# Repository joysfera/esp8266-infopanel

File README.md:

# esp8266-infopanel
WiFi LED information panel built on ESP8266

Using either WS2812 kind of LED strip or MAX7219 based LED matrix modules.

Video presentation in Czech language here: https://youtu.be/nCY0f-b_-vU

Updated exactly a year later for OpenAlt 2019 - added complete application
"clock" using NodeMCU modules u8g2d, sntp, rtctime and enduser_setup.

MicroUSB connector that fits to the PCB is BI0001715, found e.g. here https://www.aliexpress.com/i/32763236347.html

petr@pstehlik.cz

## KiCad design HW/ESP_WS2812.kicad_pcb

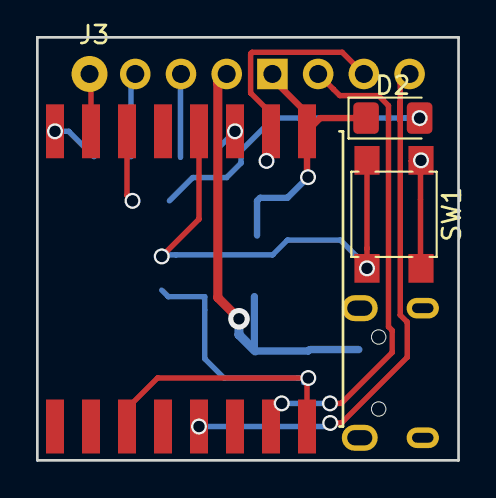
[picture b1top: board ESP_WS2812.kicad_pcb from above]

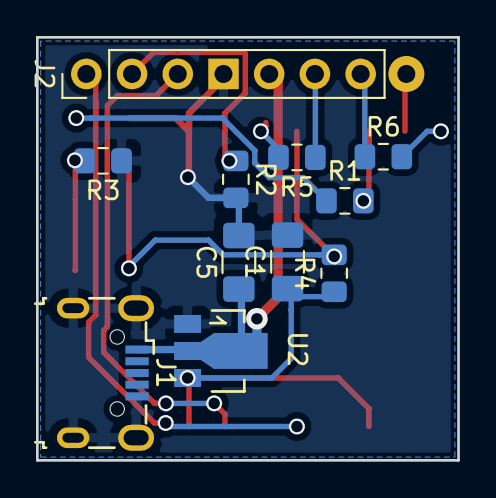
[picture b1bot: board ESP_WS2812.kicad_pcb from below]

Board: 2 copper layers, 23.4 x 23.5 mm, 15 parts (11 on the bottom side), 15 nets.

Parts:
C1, C5: 10µF; C_1206_3216Metric_Pad1.42x1.75mm_HandSolder
D2: LED; D_1206_3216Metric_Pad1.42x1.75mm_HandSolder
J1: USB_B_Micro; USB_Micro-B_Wuerth_629105150521
J2: Display; PinHeader_1x07_P2.54mm_Vertical
J3: RX; SolderWirePad_1x01_Drill0.8mm
R1, R3, R5, R6: 330; R_0805_2012Metric_Pad1.15x1.40mm_HandSolder
R2, R4: 10k; R_0805_2012Metric_Pad1.15x1.40mm_HandSolder
SW1: User; SW_SPST_TL3305A
U1: ESP8266-07; ESP-8266-07
U2: HT7335; SOT89-3_Housing

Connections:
/CLK: J2.1, U1.5
/CS: J2.2, R2.1, U1.10
/DIN: J2.3, U1.7
/TX1: J2.7, R6.1
/TX2: J2.6, R5.1
/VCC: C5.1, J1.1, J2.5, U2.2
GND: C1.2, C5.2, D2.1, J1.5, J1.6, J2.4, R2.2, R3.1, U1.9, U2.1
unnamed: C1.1, R4.1, U1.3, U1.8, U2.3
unnamed: D2.2, R1.1
unnamed: J3.1, U1.15
unnamed: R1.2, U1.14
unnamed: R3.2, SW1.1
unnamed: R4.2, SW1.2, U1.12
unnamed: R5.2, U1.11
unnamed: R6.2, U1.16

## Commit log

2018-10-31 schematics and PCB exported from KiCad
2018-11-02 small demos prepared for OpenAlt
2018-11-02 not enough information yet
2018-11-05 demos updated
2018-11-05 Video URL added
2018-11-05 KiCad files, revision 2 (Schottky diode removed, HT7335 used instead)
2019-11-01 added complete application displaying current time thanks to SNTP
2020-06-27 microUSB connector type documented
